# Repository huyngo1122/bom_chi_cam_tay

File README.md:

# Arduino_Project
Mo ta project .

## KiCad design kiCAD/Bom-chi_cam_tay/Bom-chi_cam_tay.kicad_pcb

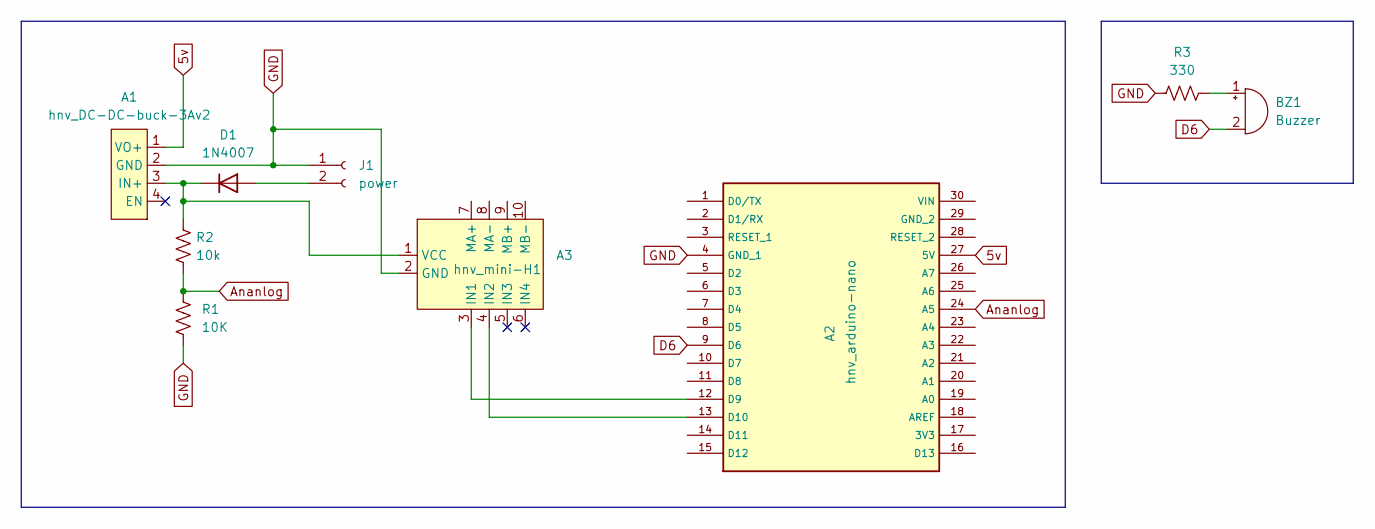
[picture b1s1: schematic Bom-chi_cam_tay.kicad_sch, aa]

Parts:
A1: hnv_DC-DC-buck-3Av2; DC-DC-buck-3Av2
A2: hnv_arduino-nano; hnv_arduino_nano
A3: hnv_mini-H1; hnv_mini_H1
BZ1: Buzzer; Buzzer_12x9.5RM7.6
D1: 1N4007; D_DO-41_SOD81_P10.16mm_Horizontal
J1: power
R1: 10K; R_Axial_DIN0204_L3.6mm_D1.6mm_P7.62mm_Horizontal
R2: 10k; R_Axial_DIN0204_L3.6mm_D1.6mm_P7.62mm_Horizontal
R3: 330; R_Axial_DIN0204_L3.6mm_D1.6mm_P7.62mm_Horizontal

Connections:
5v: A1.1 (VO+), A2.27 (5V)
Ananlog: A2.24 (A5), R1.1, R2.2
D6: A2.9 (D6), BZ1.2 (+)
GND: A1.2 (GND), A2.4 (GND_1), A3.2 (GND), J1.1, R1.2, R3.2
unnamed: A2.12 (D9), A3.3 (IN1)
unnamed: A2.13 (D10), A3.4 (IN2)
unnamed: A1.3 (IN+), A3.1 (VCC), D1.1 (K), R2.1
unnamed: BZ1.1 (-), R3.1
unnamed: D1.2 (A), J1.2

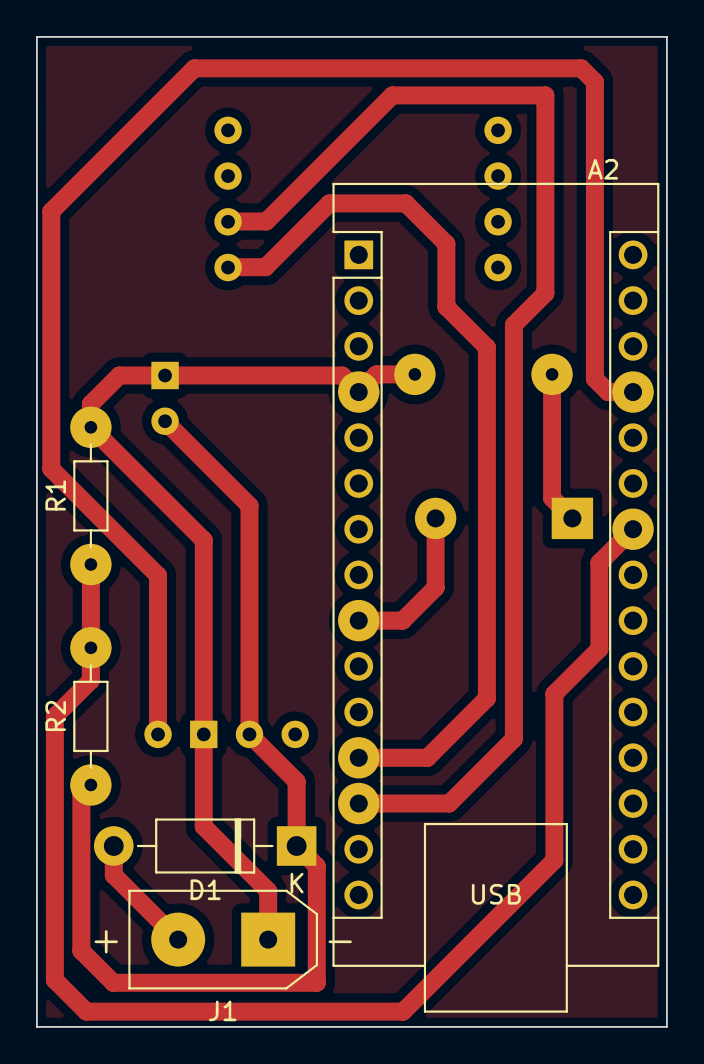
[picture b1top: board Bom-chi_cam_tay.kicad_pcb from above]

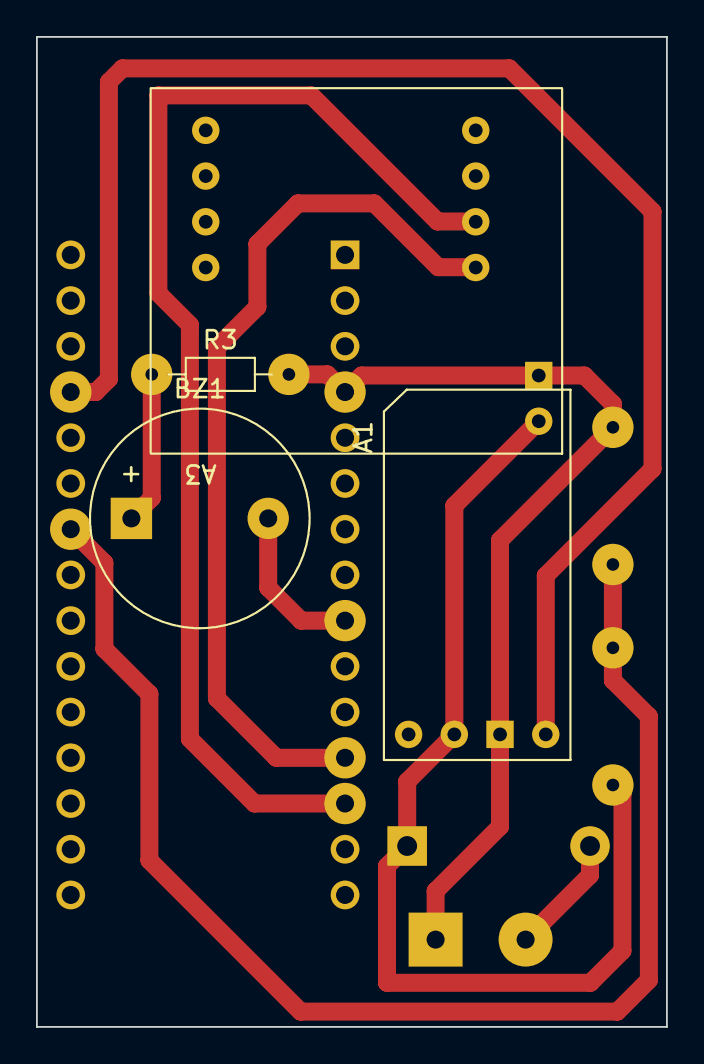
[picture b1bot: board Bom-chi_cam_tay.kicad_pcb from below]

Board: 2 copper layers, 35.0 x 55.0 mm, 9 parts (4 on the bottom side), 9 nets.

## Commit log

2023-01-12 test_uln2003 da quay duoc
2023-02-01 cap nhat 1/2/2023
2023-02-07 update pcb 7/2/2023
